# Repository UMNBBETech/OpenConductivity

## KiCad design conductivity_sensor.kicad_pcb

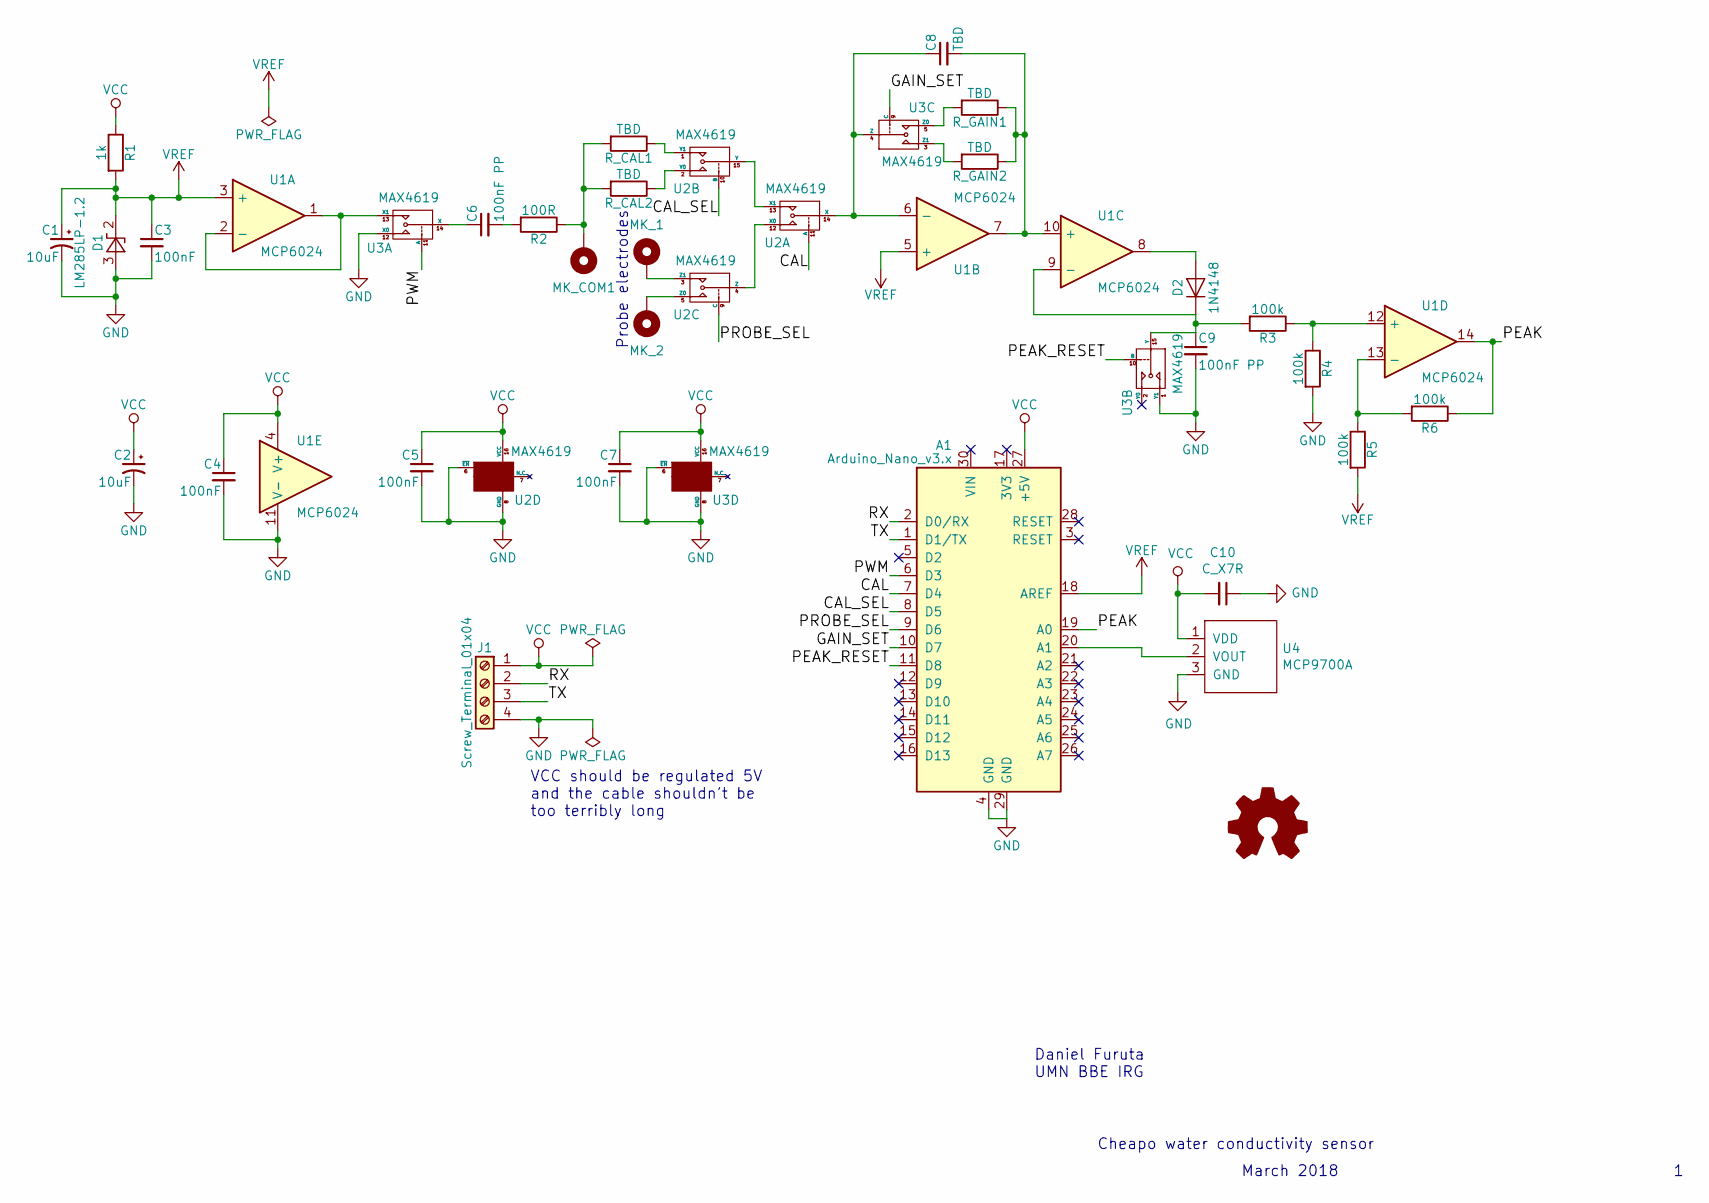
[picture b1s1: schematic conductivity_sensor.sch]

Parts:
A1: Arduino_Nano_v3.x; Arduino_Nano
C1, C2: 10uF; CP_TH_RADIAL_D5.0mm_P2.00mm
C3, C4, C5, C7: 100nF; C_TH_CERAMIC_RADIAL_100mil
C6, C9: 100nF PP; C_FILM_L10.3mm_W5.0mm_P7.50mm
C8: TBD; C_TH_CERAMIC_RADIAL_100mil
C10: C_X7R; C_TH_CERAMIC_RADIAL_100mil
D1: LM285LP-1.2; TO-92
D2: 1N4148; DO-35
J1: Screw_Terminal_01x04; TerminalBlock_04x3.5mm_Straight
MK_1, MK_2: Mounting_Hole_PAD; 4-40 screw terminal keystone 7774
MK_COM1: Mounting_Hole_PAD; 4-40 screw terminal keystone 7774
R1: 1k; R_TH_0.25W_400mil
R2: 100R; R_TH_0.25W_400mil
R3, R4, R5, R6: 100k; R_TH_0.25W_400mil
R_CAL1, R_CAL2: TBD; R_TH_0.25W_400mil
R_GAIN1, R_GAIN2: TBD; R_TH_0.25W_400mil
U1: MCP6024; DIP-14
U2, U3: MAX4619; DIP-16
U4: MCP9700A; TO-92

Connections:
/CAL: A1.7 (D4), U2.11 (A)
/CAL_SEL: A1.8 (D5), U2.10 (B)
/GAIN_SET: A1.10 (D7), U3.9 (C)
/PEAK: A1.19 (A0), R6.1, U1.14
/PEAK_RESET: A1.11 (D8), U3.10 (B)
/PROBE_SEL: A1.9 (D6), U2.9 (C)
/PWM: A1.6 (D3), U3.11 (A)
/RX: A1.2 (D0/RX), J1.2
/TX: A1.1 (D1/TX), J1.3
GND: A1.4 (GND), A1.29 (GND), C1.2, C2.2, C3.2, C4.2, C5.2, C7.2, C9.2, C10.1, D1.3 (A), J1.4, R4.2, U1.11 (V-), U2.6 (~EN), U2.8 (GND), U3.1 (Y1), U3.6 (~EN), U3.8 (GND), U3.12 (X0), U4.3 (GND)
unnamed: A1.20 (A1), U4.2 (VOUT)
unnamed: C6.1, U3.14 (X)
unnamed: C6.2, R2.2
unnamed: C8.1, U1.6 (-), U2.14 (X), U3.4 (Z)
unnamed: C8.2, R_GAIN1.1, R_GAIN2.1, U1.7, U1.10 (+)
unnamed: C9.1, D2.1 (K), R3.2, U1.9 (-), U3.15 (Y)
unnamed: D2.2 (A), U1.8
unnamed: MK_1.1, U2.3 (Z1)
unnamed: MK_2.1, U2.5 (Z0)
unnamed: MK_COM1.1, R2.1, R_CAL1.2, R_CAL2.2
unnamed: R3.1, R4.1, U1.12 (+)
unnamed: R5.1, R6.2, U1.13 (-)
unnamed: R_CAL1.1, U2.1 (Y1)
unnamed: R_CAL2.1, U2.2 (Y0)
unnamed: R_GAIN1.2, U3.5 (Z0)
unnamed: R_GAIN2.2, U3.3 (Z1)
unnamed: U1.1, U1.2 (-), U3.13 (X1)
unnamed: U2.4 (Z), U2.12 (X0)
unnamed: U2.13 (X1), U2.15 (Y)
VCC: A1.27 (+5V), C2.1, C4.1, C5.1, C7.1, C10.2, J1.1, R1.1, U1.4 (V+), U2.16 (VCC), U3.16 (VCC), U4.1 (VDD)
VREF: A1.18 (AREF), C1.1, C3.1, D1.2 (K), R1.2, R5.2, U1.3 (+), U1.5 (+)

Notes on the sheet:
Probe electrodes
VCC should be regulated 5V and the cable shouldn't be too terribly long
Cheapo water conductivity sensor
March 2018
Daniel Furuta UMN BBE IRG

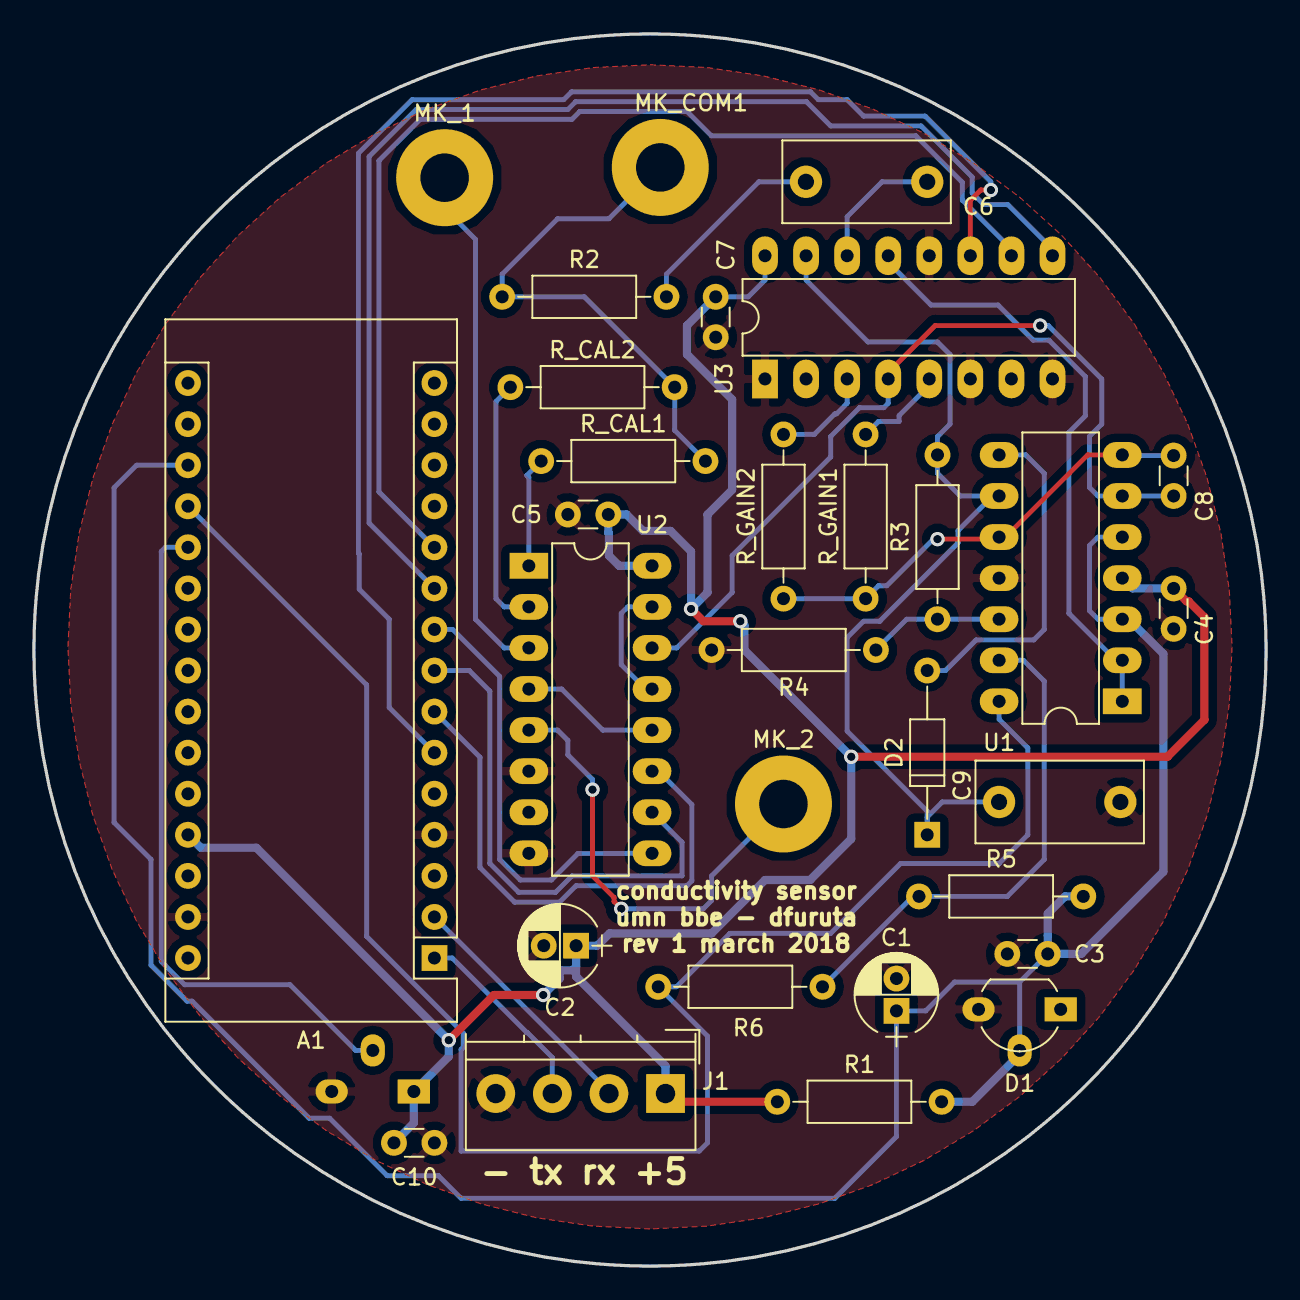
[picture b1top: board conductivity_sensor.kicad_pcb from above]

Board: 2 copper layers, 76.2 x 76.2 mm, 31 parts (1 on the bottom side), 31 nets.

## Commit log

2018-03-12 first commit
    initial schematic for open conductivity sensor
2018-03-14 mostly there
2018-03-14 almost there
2018-03-20 first version
